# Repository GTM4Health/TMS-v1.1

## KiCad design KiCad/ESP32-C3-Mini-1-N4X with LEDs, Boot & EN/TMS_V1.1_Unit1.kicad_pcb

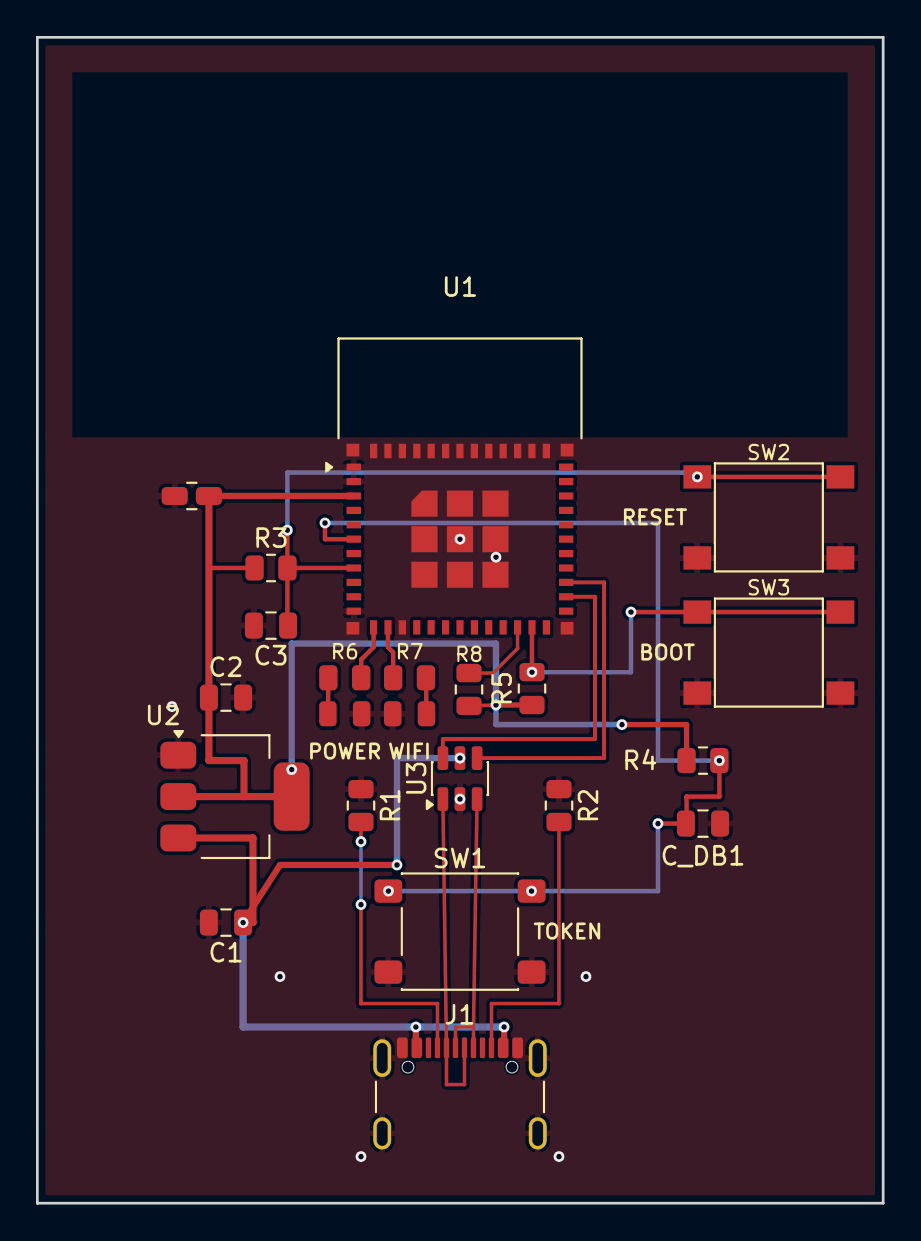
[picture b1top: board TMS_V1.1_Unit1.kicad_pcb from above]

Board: 2 copper layers, 47.0 x 64.8 mm, 22 parts (0 on the bottom side), 17 nets.

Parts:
C1: 10uF; C_0805_2012Metric
C2: 22uF; C_0805_2012Metric
C3, C4: 100nF; C_0805_2012Metric
C_DB1: 100nF; C_0805_2012Metric
D1: Power (Red); LED_0805_2012Metric
D2: WiFi (Green); LED_0805_2012Metric
J1: USB4105-GF-A; USB_C_Receptacle_GCT_USB4105-xx-A_16P_TopMnt_Horizontal
R1, R2: 5.1k; R_0805_2012Metric
R3, R4, R5, R8: 10k; R_0805_2012Metric
R6, R7: 470; R_0805_2012Metric
SW1: TOKEN_BTN; SW_SPST_PTS645Sx43SMTR92
SW2: RESET; SW_SPST_PTS645Sx43SMTR92
SW3: Boot; SW_SPST_PTS645Sx43SMTR92
U1: ESP32-C3-MINI-1; ESP32C3MINI1N4X
U2: AMS1117-3.3; SOT-223-3_TabPin2
U3: USBLC6-2SC6; SOT-23-6

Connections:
/3V3: C2.1, C4.1, R3.1, R4.1, R5.1, R8.1, U1.3, U2.2 (VO)
/BOOT: R5.2, SW3.1, U1.23
/POWER LED: R6.1, U1.12
/RESET: C3.1, R3.2, SW2.1, U1.8
/TG: C_DB1.1, R4.2, SW1.1, U1.6
/USB C: C1.1, J1.A4, J1.A9, J1.B4, J1.B9, U2.3 (VI), U3.5 (VBUS)
/USB_D+: U1.27, U3.4 (I/O2)
/USB_D-: U1.26, U3.6 (I/O1)
/WIFI LED: R7.1, U1.13
GND: C1.2, C2.2, C3.2, C4.2, C_DB1.2, D1.1, D2.1, J1.A1, J1.A12, J1.B1, J1.B12, J1.SH, R1.1, R2.1, SW1.2, SW2.2, SW3.2, U1.1, U1.2, U1.11, U1.14, U1.36, U1.37, U1.38, U1.39, U1.40, U1.41, U1.42, U1.43, U1.44, U1.45, U1.46, U1.47, U1.48, U1.49, U1.50, U1.51, U1.52, U1.53, U2.1 (GND), U3.2 (GND)
unnamed: D1.2, R6.2
unnamed: D2.2, R7.2
unnamed: J1.A5, R1.2
unnamed: J1.B5, R2.2
unnamed: J1.A6, J1.B6, U3.3 (I/O2)
unnamed: J1.A7, J1.B7, U3.1 (I/O1)
unnamed: R8.2, U1.22

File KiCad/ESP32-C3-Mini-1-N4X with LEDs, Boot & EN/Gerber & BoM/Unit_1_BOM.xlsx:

Item # | Designator(s) | Qty | Value | Package / Footprint | Manufacturer | Manufacturer Part Number (MPN) | Description | Procurement Link
1 | C1 | 1 | 10uF | 0805 (2012 Metric) | Samsung Electro-Mechanics | CL21B106KOQNFNE | Capacitor Ceramic MLCC 10µF 16V X7R ±10% SMD 0805 | https://robu.in/product/cl21b106koqnfne-samsung-cap-ceramic-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
2 | C2 | 1 | 22uF | 0805 (2012 Metric) | Guangdong Fenghua Advanced Tech (FH) | 0805X226M160NT | Capacitor Ceramic MLCC 22µF 16V X5R ±20% SMD 0805 | https://robu.in/product/0805x226m160nt-fh-16v-22uf-x5r%c2%b1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
3 | C3 | 1 | 1uF | 0805 (2012 Metric) | Murata Electronics | GCM21BR71E105KA56K | Capacitor Ceramic MLCC 1µF 25V X7R ±10% SMD 0805 Automotive AEC-Q200 | https://robu.in/product/gcm21br71e105ka56k-murata-electronic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
4 | C4, C_DB1 | 2 | 100nF | 0805 (2012 Metric) | Yageo | CC0805KKX7R0BB104 | Capacitor Ceramic MLCC 100nF (0.1µF) 100V X7R ±10% SMD 0805 | https://robu.in/product/cc0805kkx7r0bb104-yageo-100v-100nf-x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
5 | D1 | 1 | LED (Red) | 0805 (2012 Metric) | Generic / Robu | 0805-LED-RED | SMD Chip LED 0805 Red | https://robu.in/product/0805-surface-mount-led-red-50-pcs/
6 | D2 | 1 | LED (Green) | 0805 (2012 Metric) | Generic / Robu | 0805-LED-GREEN | SMD Chip LED 0805 Green | https://robu.in/product/0805-surface-mount-led-green-50-pcs/
7 | J1 | 1 | USB4105-GF-A | USB-C 16-Pin SMD Top-Mount Horizontal (GCT USB4105 style) | GCT | USB4105-GF-A | USB 2.0 Type-C Receptacle 16-Pin Horizontal Top-Mount, SMT + TH Shell Tabs, 20k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 | https://www.mouser.in/ProductDetail/GCT/USB4105-GF-A?qs=KUoI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
8 | R1, R2 | 2 | 5.1kΩ | 0805 (2012 Metric) | Yageo | AC0805FR-075K1L | Resistor Thick Film 5.1kΩ ±1% 1/8W SMD 0805 Automotive AEC-Q200 | https://robu.in/product/ac0805fr-075k1l-yageo-res-thick-film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
9 | R3, R4, R5, R8 | 4 | 10kΩ | 0805 (2012 Metric) | Yageo | AC0805FR-0710KL | Resistor Thick Film 10kΩ ±1% 1/8W SMD 0805 Automotive AEC-Q200 | https://robu.in/product/ac0805fr-0710kl-yageo-res-thick-film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
10 | R6, R7 | 2 | 470Ω | 0805 (2012 Metric) | Yageo | RC0805FR-07470RL | Resistor Thick Film 470Ω ±1% 1/8W SMD 0805 ±100ppm/°C | https://robu.in/product/rc0805fr-07470rl-yageo-res-thick-fil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
11 | SW1 | 1 | TOKEN_BTN | SMD 6x6mm (PTS645) | C&K / Littelfuse | PTS645SL13SMTR92LFS | Tactile Switch SPST-NO SMD 6x6mm, Actuator Height 13mm, 160gf (Token Button) | https://robu.in/product/pts645sl13smtr92lfs-ck-smd6x6mm-tact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
12 | SW2, SW3 | 2 | Tactile Switch (EN, Boot) | SMD 6x6mm (PTS645) | C&K / Littelfuse | PTS645SM43SMTR92LFS | Tactile Switch SPST-NO SMD 6x6mm, Actuator Height 4.3mm, 160gf (EN & Boot) | https://robu.in/product/pts645sm43smtr92lfs-ck-6mm-4-3mm-rou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
13 | U1 | 1 | ESP32-C3-MINI-1-N4X | Module SMD (ESP32C3MINI1N4X) | Espressif Systems | ESP32-C3-MINI-1-N4X | WiFi & BLE 5.0 Module, ESP32-C3FN4 RISC-V 160MHz, 4MB Flash, PCB Antenna | https://www.mouser.in/ProductDetail/Espressif-Systems/ESP32-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
14 | U2 | 1 | AMS1117-3.3 | SOT-223-3 (Tab Pin 2) | Advanced Monolithic Systems / Kexin | AMS1117-3.3 | LDO Voltage Regulator, Fixed 3.3V Output, 1A Max Current, SOT-223 | https://robu.in/product/ams1117-3-3-kexin-1a-fixed-3-3v-posi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
15 | U3 | 1 | USBLC6-2SC6 | SOT-23-6 | STMicroelectronics | USBLC6-2SC6 | Very low capacitance ESD protection diode array, 2 data-line, SOT-23-6 | https://www.mouser.in/ProductDetail/STMicroelectronics/USBLC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

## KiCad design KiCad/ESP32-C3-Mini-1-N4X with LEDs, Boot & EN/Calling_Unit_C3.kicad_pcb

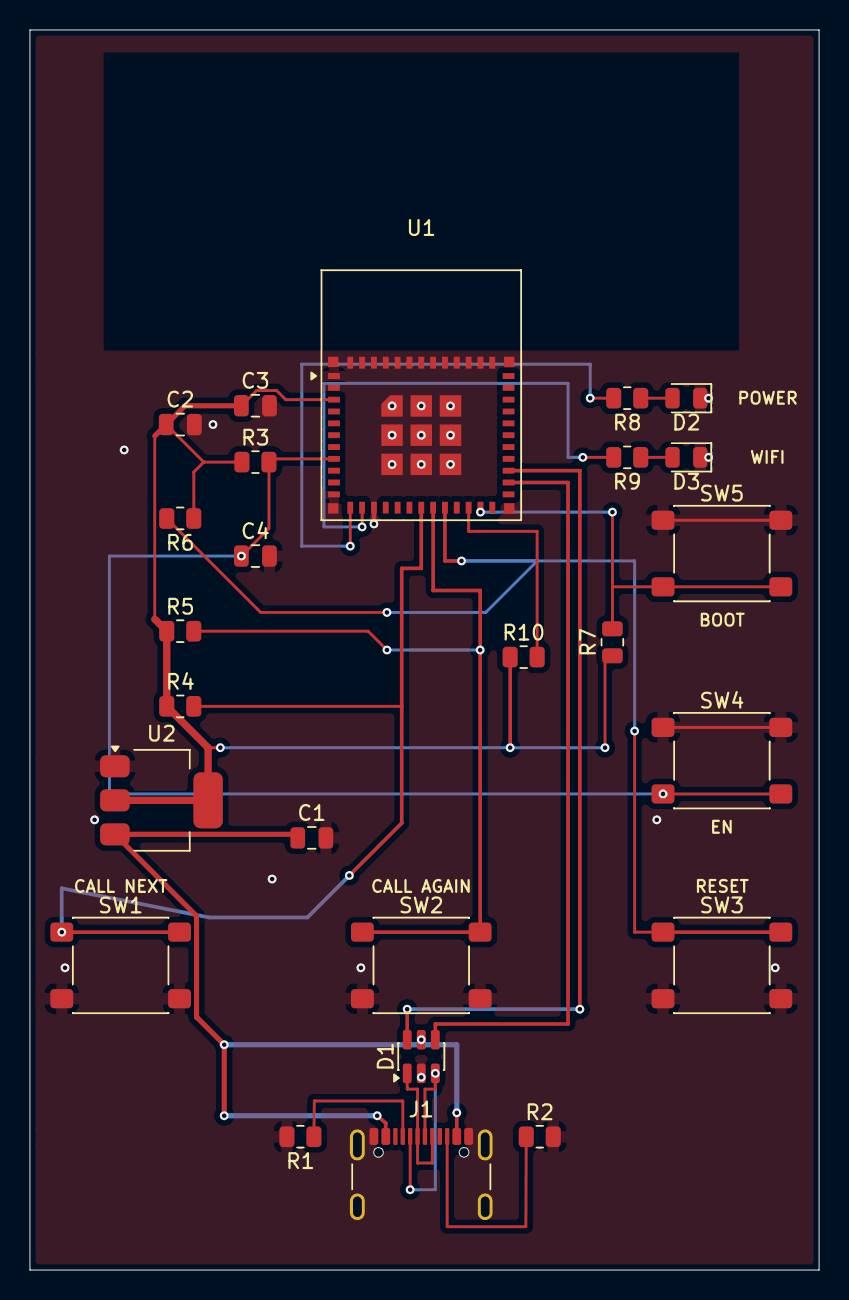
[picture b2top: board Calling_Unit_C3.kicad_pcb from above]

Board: 2 copper layers, 53.3 x 83.8 mm, 25 parts (0 on the bottom side), 19 nets.

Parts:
C1, C2, C3: C_0805_2012Metric
C4: 1uF; C_0805_2012Metric
D1: SOT-23-6
D2: Power (Red); LED_0805_2012Metric
D3: WiFi (Green); LED_0805_2012Metric
J1: USB_C_Receptacle_GCT_USB4105-xx-A_16P_TopMnt_Hori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; USB_C_Receptacle_GCT_USB4105-xx-A_16P_TopMnt_Horizontal
R1, R2: 5.1k; R_0805_2012Metric
R3, R4, R5, R6: R_0805_2012Metric
R7, R10: 10k; R_0805_2012Metric
R8, R9: 470; R_0805_2012Metric
SW1, SW2, SW3: SW_SPST_PTS645Sx43SMTR92
SW4: EN; SW_SPST_PTS645Sx43SMTR92
SW5: Boot; SW_SPST_PTS645Sx43SMTR92
U1: ESP32-C3-MINI-1; ESP32C3MINI1N4X
U2: SOT-223-3_TabPin2

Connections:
/3V3: C2.1, C3.1, R3.1, R4.1, R5.1, R6.1, R7.1, R10.1, U1.3, U2.2
/Call Again: R5.2, SW2.1, U1.19
/Call Next: R4.2, SW1.1, U1.18
/Reset: R6.2, SW3.1, U1.20
/USB C: C1.1, D1.5, J1.A4, J1.A9, J1.B4, J1.B9, U2.3
/USB_D+: D1.6, U1.27
/USB_D-: D1.4, U1.26
GND: C1.2, C2.2, C3.2, C4.2, D1.2, D2.1, D3.1, J1.A1, J1.A12, J1.B1, J1.B12, J1.SH, R1.2, R2.2, SW1.2, SW2.2, SW3.2, SW4.1, SW5.1, U1.1, U1.2, U1.11, U1.14, U1.36, U1.37, U1.38, U1.39, U1.40, U1.41, U1.42, U1.43, U1.44, U1.45, U1.46, U1.47, U1.48, U1.49, U1.50, U1.51, U1.52, U1.53, U2.1
unnamed: D1.1, J1.A6, J1.B6
unnamed: D1.3, J1.A7, J1.B7
unnamed: D2.2, R8.1
unnamed: D3.2, R9.1
unnamed: J1.A5, R1.1
unnamed: J1.B5, R2.1
unnamed: R7.2, SW5.2, U1.23
unnamed: R8.2, U1.12
unnamed: R9.2, U1.13
unnamed: R10.2, U1.22
unnamed: C4.1, R3.2, SW4.2, U1.8

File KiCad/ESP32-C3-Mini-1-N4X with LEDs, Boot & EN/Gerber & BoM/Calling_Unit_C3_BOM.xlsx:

Item # | Designator(s) | Qty | Value | Footprint | Manufacturer | Manufacturer Part Number (MPN) | Description | Procurement Link
1 | C1 | 1 | 10uF | 0805 (2012 Metric) | Samsung Electro-Mechanics | CL21B106KOQNFNE | Capacitor Ceramic MLCC 10µF 16V X7R ±10% SMD 0805 | https://robu.in/product/cl21b106koqnfne-samsung-cap-ceramic-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
2 | C2 | 1 | 22uF | 0805 (2012 Metric) | Guangdong Fenghua Advanced Tech (FH) | 0805X226M160NT | Capacitor Ceramic MLCC 22µF 16V X5R ±20% SMD 0805 | https://robu.in/product/0805x226m160nt-fh-16v-22uf-x5r%c2%b1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
3 | C3 | 1 | 100nF | 0805 (2012 Metric) | Yageo | CC0805KKX7R0BB104 | Capacitor Ceramic MLCC 100nF (0.1µF) 100V X7R ±10% SMD 0805 | https://robu.in/product/cc0805kkx7r0bb104-yageo-100v-100nf-x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
4 | C4 | 1 | 1uF | 0805 (2012 Metric) | Murata Electronics | GCM21BR71E105KA56K | Capacitor Ceramic MLCC 1µF 25V X7R ±10% SMD 0805 Automotive AEC-Q200 | https://robu.in/product/gcm21br71e105ka56k-murata-electronic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
5 | D1 | 1 | USBLC6-2SC6 | SOT-23-6 | STMicroelectronics | USBLC6-2SC6 | Very low capacitance ESD protection diode array, 2 data-line, SOT-23-6 | https://www.mouser.in/ProductDetail/STMicroelectronics/USBLC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
6 | D2 | 1 | Power LED (Red) | 0805 (2012 Metric) | Generic / Robu | 0805-LED-RED | Power Indicator LED 0805 Red (SMD) | https://robu.in/product/0805-surface-mount-led-red-50-pcs/
7 | D3 | 1 | WiFi LED (Green) | 0805 (2012 Metric) | Generic / Robu | 0805-LED-GREEN | WiFi Status LED 0805 Green (SMD) | https://robu.in/product/0805-surface-mount-led-green-50-pcs/
8 | J1 | 1 | USB_C_Receptacle_USB2.0_16P | USB-C 16-Pin SMD Top-Mount Horizontal (GCT USB4105 style) | GCT | USB4105-GF-A | USB 2.0 Type-C Receptacle 16-Pin Horizontal Top-Mount, SMT + TH Shell Tabs | https://www.mouser.in/ProductDetail/GCT/USB4105-GF-A?qs=KUoI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
9 | R1, R2 | 2 | 5.1kΩ | 0805 (2012 Metric) | Yageo | AC0805FR-075K1L | Resistor Thick Film 5.1kΩ ±1% 1/8W SMD 0805 Automotive AEC-Q200 | https://robu.in/product/ac0805fr-075k1l-yageo-res-thick-film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
10 | R3, R4, R5, R6, R7, R10 | 6 | 10kΩ | 0805 (2012 Metric) | Yageo | AC0805FR-0710KL | Resistor Thick Film 10kΩ ±1% 1/8W SMD 0805 Automotive AEC-Q200 | https://robu.in/product/ac0805fr-0710kl-yageo-res-thick-film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
11 | R8, R9 | 2 | 470Ω | 0805 (2012 Metric) | Yageo | RC0805FR-07470RL | Resistor Thick Film 470Ω ±1% 1/8W SMD 0805 ±100ppm/°C | https://robu.in/product/rc0805fr-07470rl-yageo-res-thick-fil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
12 | SW1, SW2, SW3 | 3 | Tactile Switch (Call Next, Call Again, Reset) | SMD 6x6mm (PTS645) | C&K / Littelfuse | PTS645SL13SMTR92LFS | Tactile Switch SPST-NO SMD 6x6mm, Actuator Height 13mm, 160gf | https://robu.in/product/pts645sl13smtr92lfs-ck-smd6x6mm-tact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
13 | SW4, SW5 | 2 | Tactile Switch (EN, Boot) | SMD 6x6mm (PTS645) | C&K / Littelfuse | PTS645SM43SMTR92LFS | Tactile Switch SPST-NO SMD 6x6mm, Actuator Height 4.3mm, 160gf (EN & Boot) | https://robu.in/product/pts645sm43smtr92lfs-ck-6mm-4-3mm-rou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
14 | U1 | 1 | ESP32-C3-MINI-1-N4X | Module SMD (ESP32C3MINI1N4X) | Espressif Systems | ESP32-C3-MINI-1-N4X | WiFi & BLE 5.0 Module, ESP32-C3FN4 RISC-V 160MHz, 4MB Flash, PCB Antenna | https://www.mouser.in/ProductDetail/Espressif-Systems/ESP32-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
15 | U2 | 1 | AMS1117-3.3 | SOT-223-3 (Tab Pin 2) | Advanced Monolithic Systems / Kexin | AMS1117-3.3 | LDO Voltage Regulator, Fixed 3.3V Output, 1A Max Current, SOT-223 | https://robu.in/product/ams1117-3-3-kexin-1a-fixed-3-3v-posi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

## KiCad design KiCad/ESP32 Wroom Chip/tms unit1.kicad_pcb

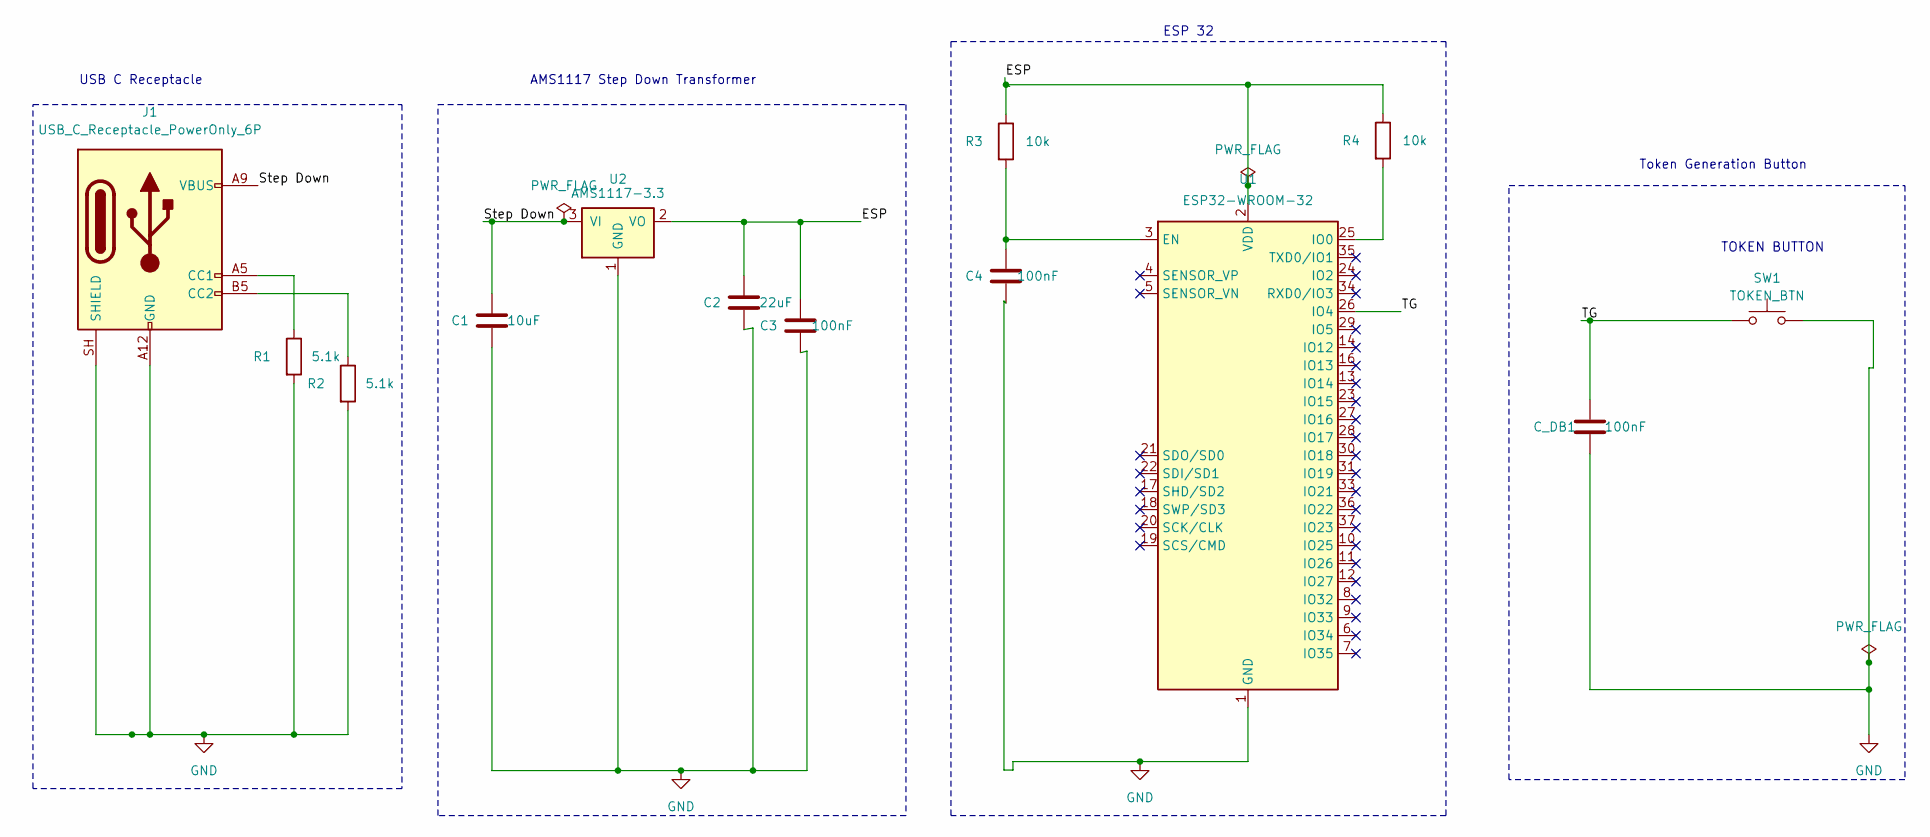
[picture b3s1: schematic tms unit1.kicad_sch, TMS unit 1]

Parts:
C1: 10uF; C_0805_2012Metric
C2: 22uF; C_0805_2012Metric
C3, C4: 100nF; C_0805_2012Metric
C_DB1: 100nF; C_0805_2012Metric
J1: USB_C_Receptacle_PowerOnly_6P; USB_C_Receptacle_GCT_USB4125-xx-x_6P_TopMnt_Horizontal
R1, R2: 5.1k; R_0805_2012Metric
R3, R4: 10k; R_0805_2012Metric
SW1: TOKEN_BTN; SW_SPST_PTS645Sx43SMTR92
U1: ESP32-WROOM-32
U2: AMS1117-3.3; SOT-223-3_TabPin2

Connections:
/ESP: C2.1, C3.1, U2.2 (VO)
/Step Down: C1.1, J1.A9 (VBUS), J1.B9 (VBUS), U2.3 (VI)
/TG: C_DB1.1, SW1.1, U1.26 (IO4)
GND: C1.2, C2.2, C3.2, C4.2, C_DB1.2, J1.A12 (GND), J1.B12 (GND), J1.SH (SHIELD), R1.2, R2.2, SW1.2, U1.1 (GND), U1.15 (GND), U1.38 (GND), U1.39 (GND), U2.1 (GND)
unnamed: J1.A5 (CC1), R1.1
unnamed: J1.B5 (CC2), R2.1
unnamed: C4.1, R3.2, U1.3 (EN)
unnamed: R4.2, U1.25 (IO0)
unnamed: R3.1, R4.1, U1.2 (VDD)

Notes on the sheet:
AMS1117 Step Down Transformer
USB C Receptacle
Token Generation Button
TOKEN BUTTON
ESP 32

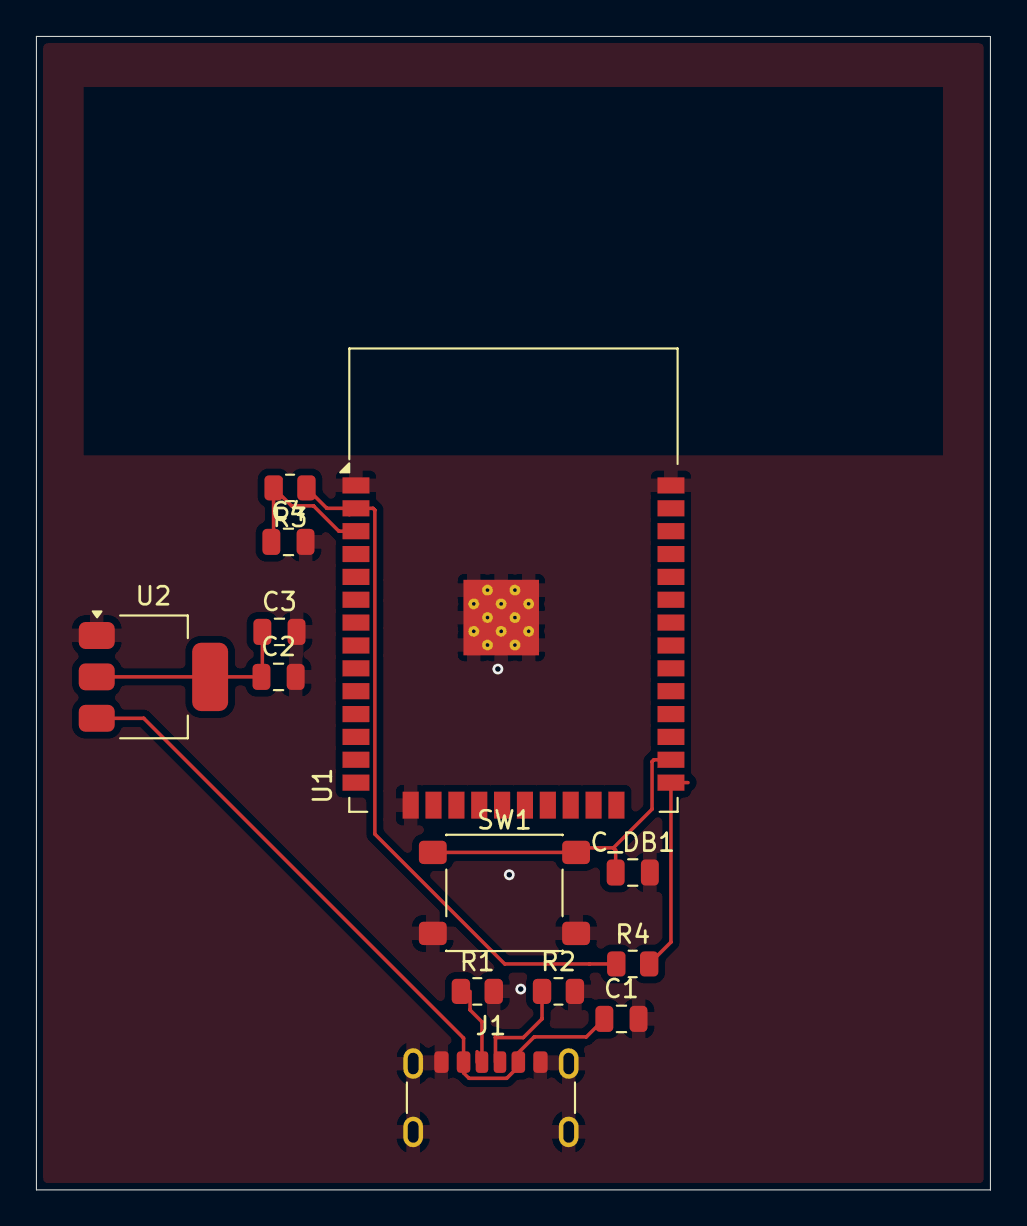
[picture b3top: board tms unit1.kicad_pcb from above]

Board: 2 copper layers, 53.0 x 64.1 mm, 13 parts (0 on the bottom side), 9 nets.

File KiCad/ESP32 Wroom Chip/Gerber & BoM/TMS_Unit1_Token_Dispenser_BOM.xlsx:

Item # | Reference | Qty | Value | Footprint / Package | Description | Manufacturer | Manufacturer Part Number (MPN) | Component Link / Source
1 | U1 | 1 | ESP32-WROOM-32 | RF_Module:ESP32-WROOM-32 | ESP32 Wi-Fi + Bluetooth SoC 38-Pin Castellated Module, 4MB Flash | Espressif Systems | ESP32-WROOM-32 (4MB) | https://robu.in/product/espressif-esp32-wroom-32-4m-32mbit-f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
2 | U2 | 1 | AMS1117-3.3 | SOT-223-3 (Tab Pin 2) | Linear Low Dropout (LDO) Positive Voltage Regulator, Fixed 3.3V, 1A | Guangdong Kexin | AMS1117-3.3V | https://robu.in/product/ams1117-3-3-kexin-1a-fixed-3-3v-posi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
3 | J1 | 1 | USB-C 6P Power-Only | Connector_USB:USB_C_Receptacle_6P | USB Type-C 6-Pin Reversible Female Connector (Power Charging, Top Mount) | Generic / Robu | USB 3.1 Type-C 6P | https://robu.in/product/usb-3-1-type-c-6-pin-for-power-charg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
4 | R1, R2 | 2 | 5.1kΩ | 0805 (2012 Metric) | Thick Film Chip Resistor, 5.1kΩ, 1%, 1/8W, 0805 (CC-line pull-downs) | Yageo | AC0805FR-075K1L | https://robu.in/product/ac0805fr-075k1l-yageo-res-thick-film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
5 | R3, R4 | 2 | 10kΩ | 0805 (2012 Metric) | Thick Film Chip Resistor, 10kΩ, 1%, 1/8W, 0805 (Pull-up resistors) | Yageo | AC0805FR-0710KL | https://robu.in/product/ac0805fr-0710kl-yageo-res-thick-film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
6 | C1 | 1 | 10µF | 0805 (2012 Metric) | Multilayer Ceramic Capacitor (MLCC), 10µF, 16V, ±10%, X7R, 0805 (LDO In) | Samsung | CL21B106KOQNFNE | https://robu.in/product/cl21b106koqnfne-samsung-cap-ceramic-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
7 | C2 | 1 | 22µF | 0805 (2012 Metric) | Multilayer Ceramic Capacitor (MLCC), 22µF, 16V, ±20%, X5R, 0805 (LDO Out) | Fenghua Advanced Tech | 0805X226M160NT | https://robu.in/product/0805x226m160nt-fh-16v-22uf-x5r%c2%b1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
8 | C3, C4, C_DB1 | 3 | 100nF | 0805 (2012 Metric) | Multilayer Ceramic Capacitor (MLCC), 100nF (0.1µF), 100V, ±10%, X7R, 0805 | Yageo | CC0805KKX7R0BB104 | https://robu.in/product/cc0805kkx7r0bb104-yageo-100v-100nf-x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
9 | SW1 | 1 | TOKEN_BTN | Button_Switch_SMD:6x6mm | Tactile Switch 6×6mm SMD, Height 4.3mm, SPST, 50mA 12V | Hanbo | TS-KG02S | https://robu.in/product/ts-kg02s-hanbo-6mm-4-3mm-50ma-round-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

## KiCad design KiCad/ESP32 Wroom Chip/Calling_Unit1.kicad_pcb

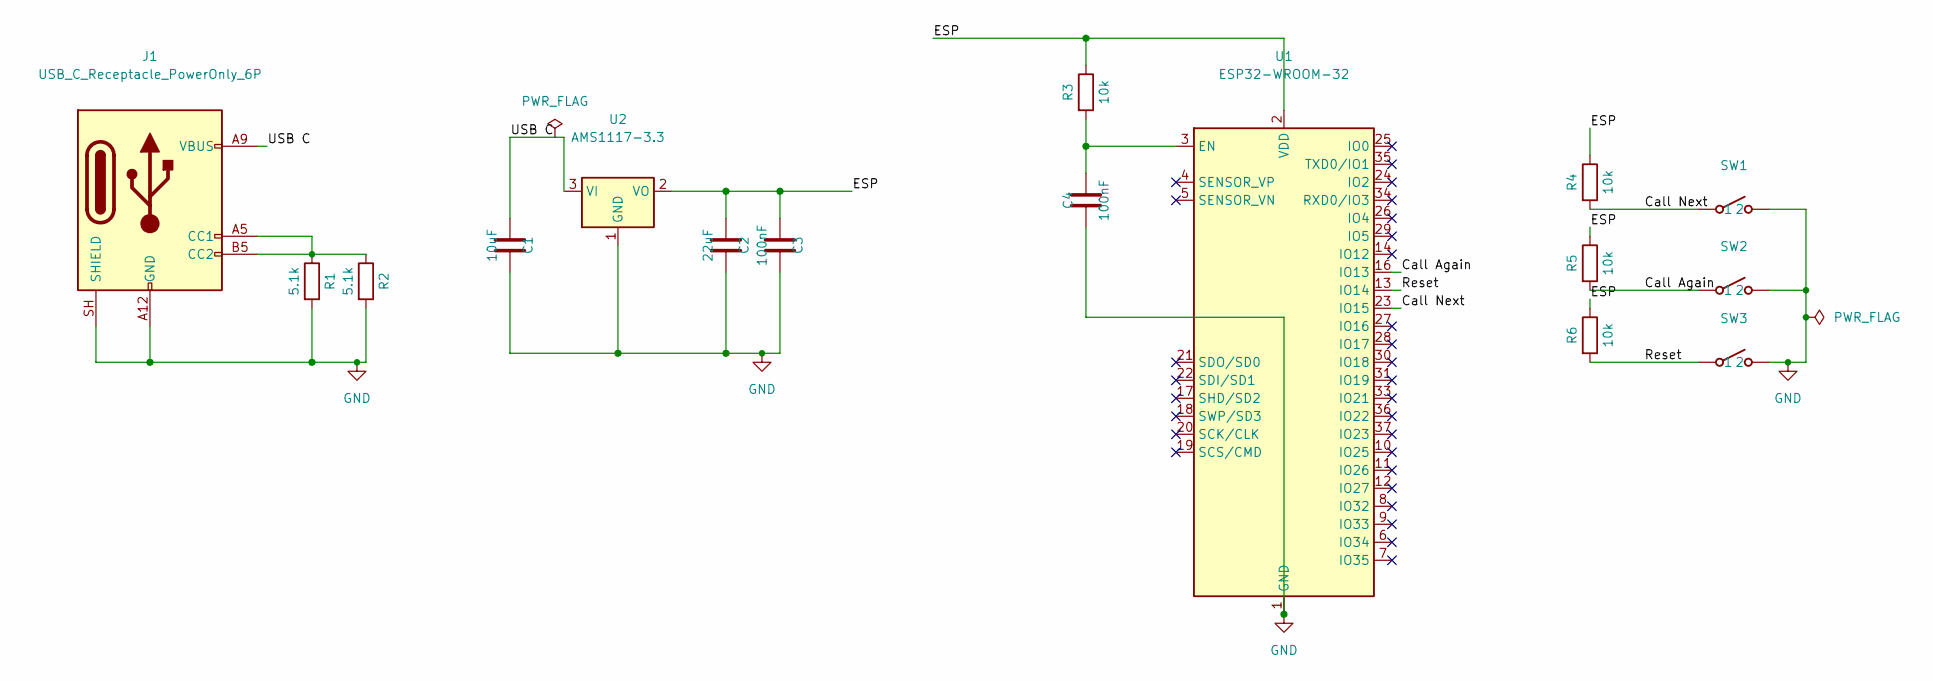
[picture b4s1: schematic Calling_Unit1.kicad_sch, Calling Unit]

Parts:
C1: 10uF; C_0805_2012Metric
C2: 22uF; C_0805_2012Metric
C3, C4: 100nF; C_0805_2012Metric
J1: USB_C_Receptacle_PowerOnly_6P; USB_C_Receptacle_GCT_USB4125-xx-x_6P_TopMnt_Horizontal
R1, R2: 5.1k; R_0805_2012Metric
R3, R4, R5, R6: 10k; R_0805_2012Metric
SW1: Call Next; SW_SPST_PTS645Sx43SMTR92
SW2: Call Again; SW_SPST_PTS645Sx43SMTR92
SW3: Reset; SW_SPST_PTS645Sx43SMTR92
U1: ESP32-WROOM-32
U2: AMS1117-3.3; SOT-223-3_TabPin2

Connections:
/Call Again: R5.2, SW2.1, U1.16 (IO13)
/Call Next: R4.2, SW1.1, U1.23 (IO15)
/ESP: C2.1, C3.1, R3.1, R4.1, R5.1, R6.1, U1.2 (VDD), U2.2 (VO)
/Reset: R6.2, SW3.1, U1.13 (IO14)
/USB C: C1.1, J1.A9 (VBUS), J1.B9 (VBUS), U2.3 (VI)
GND: C1.2, C2.2, C3.2, C4.2, J1.A12 (GND), J1.B12 (GND), J1.SH (SHIELD), R1.2, R2.2, SW1.2, SW2.2, SW3.2, U1.1 (GND), U1.15 (GND), U1.38 (GND), U1.39 (GND), U2.1 (GND)
unnamed: J1.A5 (CC1), J1.B5 (CC2), R1.1, R2.1
unnamed: C4.1, R3.2, U1.3 (EN)

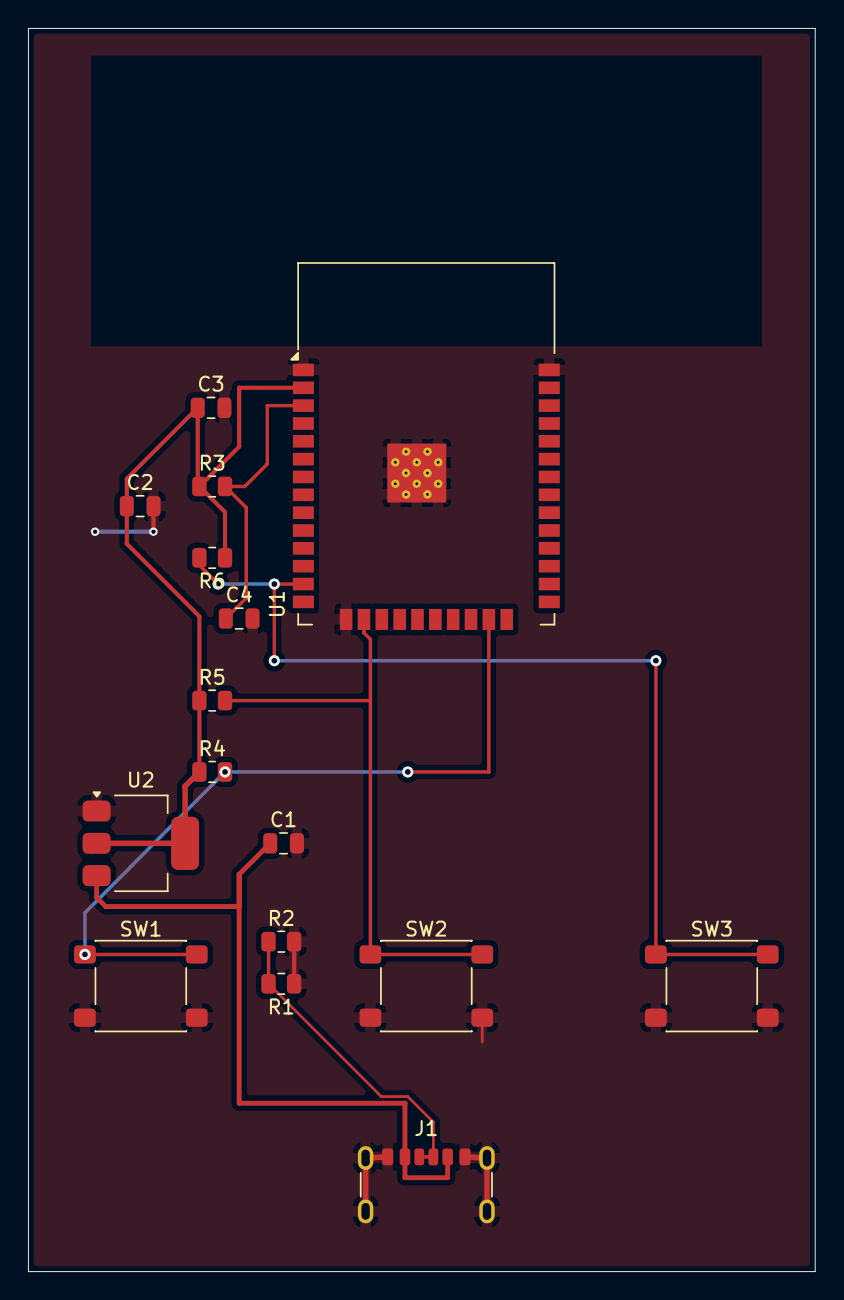
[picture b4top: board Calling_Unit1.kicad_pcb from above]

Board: 2 copper layers, 56.0 x 88.5 mm, 16 parts (0 on the bottom side), 8 nets.

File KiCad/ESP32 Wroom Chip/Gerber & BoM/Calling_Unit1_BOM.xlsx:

Item # | Designator(s) | Qty | Value | Package / Footprint | Manufacturer | Manufacturer Part Number (MPN) | Description
1 | C1 | 1 | 10uF | 0805 (2012 Metric) | Samsung Electro-Mechanics | CL21B106KOQNFNE | Capacitor Ceramic MLCC 10µF 16V X7R ±10% SMD 0805
2 | C2 | 1 | 22uF | 0805 (2012 Metric) | Guangdong Fenghua Advanced Tech (FH) | 0805X226M160NT | Capacitor Ceramic MLCC 22µF 16V X5R ±20% SMD 0805
3 | C3, C4 | 2 | 100nF | 0805 (2012 Metric) | Yageo | CC0805KKX7R0BB104 | Capacitor Ceramic MLCC 100nF (0.1µF) 100V X7R ±10% SMD 0805
4 | J1 | 1 | USB_C_Receptacle_PowerOnly_6P | USB-C 6-Pin SMD Top-Mount Horizontal (GCT USB4125 style) | GCT / Generic | TYPE-C-31-M-12 | USB 3.1 Type-C Receptacle 6-Pin SMD (Power / Charging Only, Reversible)
5 | R1, R2 | 2 | 5.1kΩ | 0805 (2012 Metric) | Yageo | AC0805FR-075K1L | Resistor Thick Film 5.1kΩ ±1% 1/8W SMD 0805 Automotive AEC-Q200
6 | R3, R4, R5, R6 | 4 | 10kΩ | 0805 (2012 Metric) | Yageo | AC0805FR-0710KL | Resistor Thick Film 10kΩ ±1% 1/8W SMD 0805 Automotive AEC-Q200
7 | SW1, SW2, SW3 | 3 | Tactile Switch (Call Next, Call Again, Reset) | SMD 6x6mm (PTS645) | C&K / Littelfuse | PTS645SL13SMTR92LFS | Tactile Switch SPST-NO SMD 6x6mm, Actuator Height 13mm, 160gf
8 | U1 | 1 | ESP32-WROOM-32 | Module SMD 38-Pin (18x25.5mm) | Espressif Systems | ESP32-WROOM-32D (4MB) | Wi-Fi & Bluetooth/BLE MCU Module, Dual Core 240MHz, 4MB Flash, PCB Antenna
9 | U2 | 1 | AMS1117-3.3 | SOT-223-3 (Tab Pin 2) | Advanced Monolithic Systems / Kexin | AMS1117-3.3 | LDO Voltage Regulator, Fixed 3.3V Output, 1A Max Current, SOT-223
